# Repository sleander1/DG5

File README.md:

# DG5
An Arduino based, Kenwood DG5 emulator for the TS-520S

For more info, see http://www.kv6o.com/wordpress/projects/kenwood-dg5-emulator/

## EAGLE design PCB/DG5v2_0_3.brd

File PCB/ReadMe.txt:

See http://www.kv6o.com/wordpress/projects/kenwood-dg5-emulator/  for instructions on how to build, and notes on the construction.

Eagle files created using Eagle 7.1.0

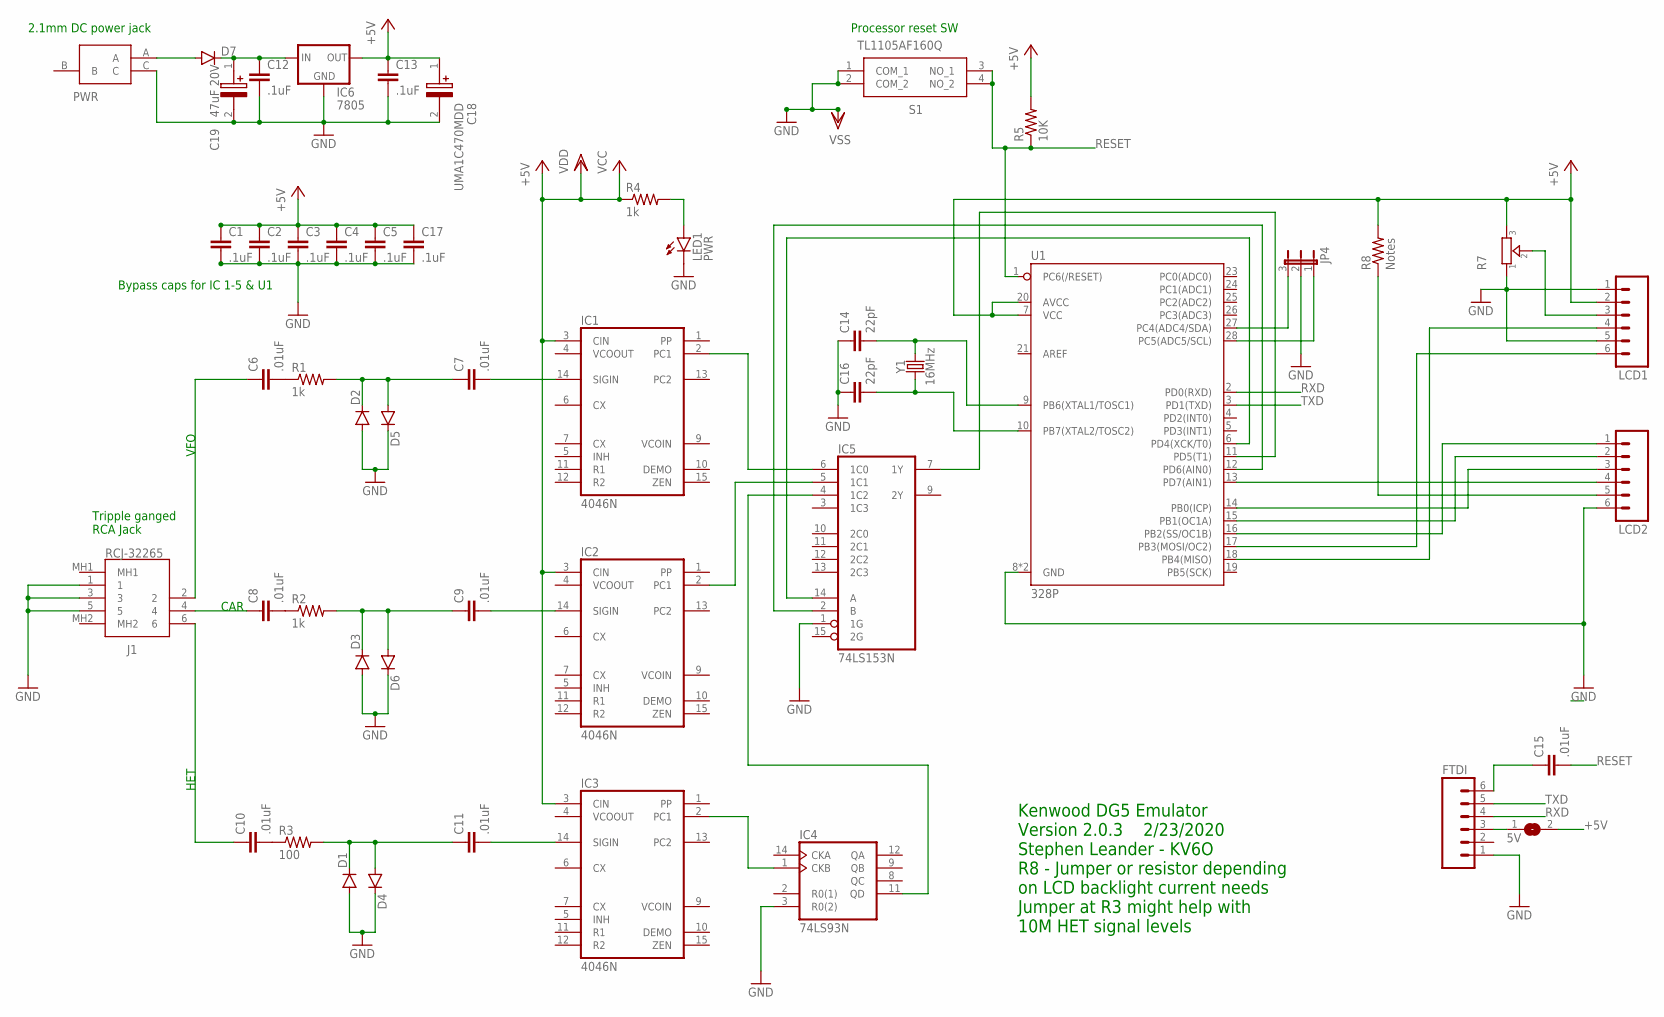
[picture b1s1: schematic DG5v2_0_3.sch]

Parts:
5V: SJ
C1, C2, C3, C4, C5, C12, C13, C17: .1uF; CAP-PTH-SMALL-KIT
C6, C7, C8, C9, C10, C11, C15: .01uF; CAP-PTH-SMALL-KIT
C14, C16: 22pF; CAP-PTH-SMALL
C18: UMA1C470MDD; CAPPRD250W45D680H600
C19: 47uF 20V; CAPPRD250W45D680H600
D1, D2, D3, D4, D5, D6: DIODE1N4148; DIODE-1N4148
D7: DIODE; DIODE-1N4001-KIT
FTDI: M06SIP; 1X06
IC1, IC2, IC3: 4046N; DIL16
IC4: 74LS93N; DIL14
IC5: 74LS153N; DIL16
IC6: 7805; TO220-IGO
J1: RCJ-32265; RCJ32265
JP4: JP2E; JP2
LCD1, LCD2: M06SIP; 1X06
LED1: PWR; LED3MM
PWR: 163-179PH-EX; 163179PHEX
R1, R2, R4: 1k; 1/6W-RES
R3: 100; 1/6W-RES
R5: 10K; 1/6W-RES
R7: TRIMMER-3306F; TRIMMER_3306F
R8: Notes; 1/6W-RES
S1: TL1105AF160Q
U1: 328P; DIP28
Y1: 16MHz; HC49US

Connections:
+5V: 5V.2, C1.1, C2.1, C3.1, C4.1, C5.1, C13.1, C17.1, C18.1 (+), IC1.3 (CIN), IC1.16 (VDD), IC2.3 (CIN), IC2.16 (VDD), IC3.3 (CIN), IC3.16 (VDD), IC4.5 (VCC), IC5.16 (VCC), IC6.OUT, LCD1.2, R4.1, R5.2, R7.3, R8.2, U1.7 (VCC), U1.20 (AVCC)
CAR: C8.1, J1.4
GND: C1.2, C2.2, C3.2, C4.2, C5.2, C12.2, C13.2, C14.1, C16.1, C17.2, C18.2 (-), C19.2 (-), D1.A, D2.A, D3.A, D4.C, D5.C, D6.C, FTDI.1, IC1.8 (VSS), IC2.8 (VSS), IC3.8 (VSS), IC4.3 (R0(2)), IC4.10 (GND), IC5.1 (1G), IC5.8 (GND), IC6.GND, J1.1, J1.3, J1.5, JP4.2, LCD1.1, LCD1.5, LCD2.6, LED1.K (C), PWR.C, R7.1, S1.1 (COM_1), S1.2 (COM_2), U1.8 (GND), U1.22 (GND)
HET: C10.1, J1.6
unnamed: C7.2, IC1.14 (SIGIN)
unnamed: IC1.2 (PC1), IC5.6 (1C0)
unnamed: IC2.2 (PC1), IC5.5 (1C1)
unnamed: C8.2, R2.1
unnamed: C6.2, R1.1
unnamed: C7.1, D2.C, D5.A, R1.2
unnamed: IC3.2 (PC1), IC4.1 (CKB)
unnamed: IC4.11 (QD), IC5.4 (1C2)
unnamed: C9.1, D3.C, D6.A, R2.2
unnamed: 5V.1, FTDI.3
unnamed: C9.2, IC2.14 (SIGIN)
unnamed: C11.2, IC3.14 (SIGIN)
unnamed: C11.1, D1.C, D4.A, R3.2
unnamed: C10.2, R3.1
unnamed: IC5.7 (1Y), U1.11 (PD5(T1))
unnamed: IC5.2 (B), U1.12 (PD6(AIN0))
unnamed: IC5.14 (A), U1.6 (PD4(XCK/T0))
unnamed: C14.2, U1.9 (PB6(XTAL1/TOSC1)), Y1.2
unnamed: LED1.A, R4.2
unnamed: JP4.3, U1.27 (PC4(ADC4/SDA))
unnamed: JP4.1, U1.28 (PC5(ADC5/SCL))
unnamed: C16.2, U1.10 (PB7(XTAL2/TOSC2)), Y1.1
unnamed: LCD2.5, R8.1
unnamed: LCD1.3, R7.2
unnamed: LCD1.4, U1.18 (PB4(MISO))
unnamed: LCD1.6, U1.17 (PB3(MOSI/OC2))
unnamed: C15.1, FTDI.6
unnamed: D7.A, PWR.A
unnamed: LCD2.1, U1.16 (PB2(SS/OC1B))
unnamed: LCD2.2, U1.15 (PB1(OC1A))
unnamed: LCD2.3, U1.14 (PB0(ICP))
unnamed: LCD2.4, U1.13 (PD7(AIN1))
RESET: C15.2, R5.1, S1.3 (NO_1), S1.4 (NO_2), U1.1 (PC6(/RESET))
RXD: FTDI.4, U1.2 (PD0(RXD))
TXD: FTDI.5, U1.3 (PD1(TXD))
VFO: C6.1, J1.2
VIN: C12.1, C19.1 (+), D7.C, IC6.IN

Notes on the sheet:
Kenwood DG5 Emulator Version 2.0.3 2/23/2020 Stephen Leander - KV6O R8 - Jumper or resistor depending on LCD backlight current needs Jumper at R3 might help with 10M HET signal levels
VFO
CAR
HET
Bypass caps for IC 1-5 & U1
Tripple ganged RCA Jack
2.1mm DC power jack
Processor reset SW

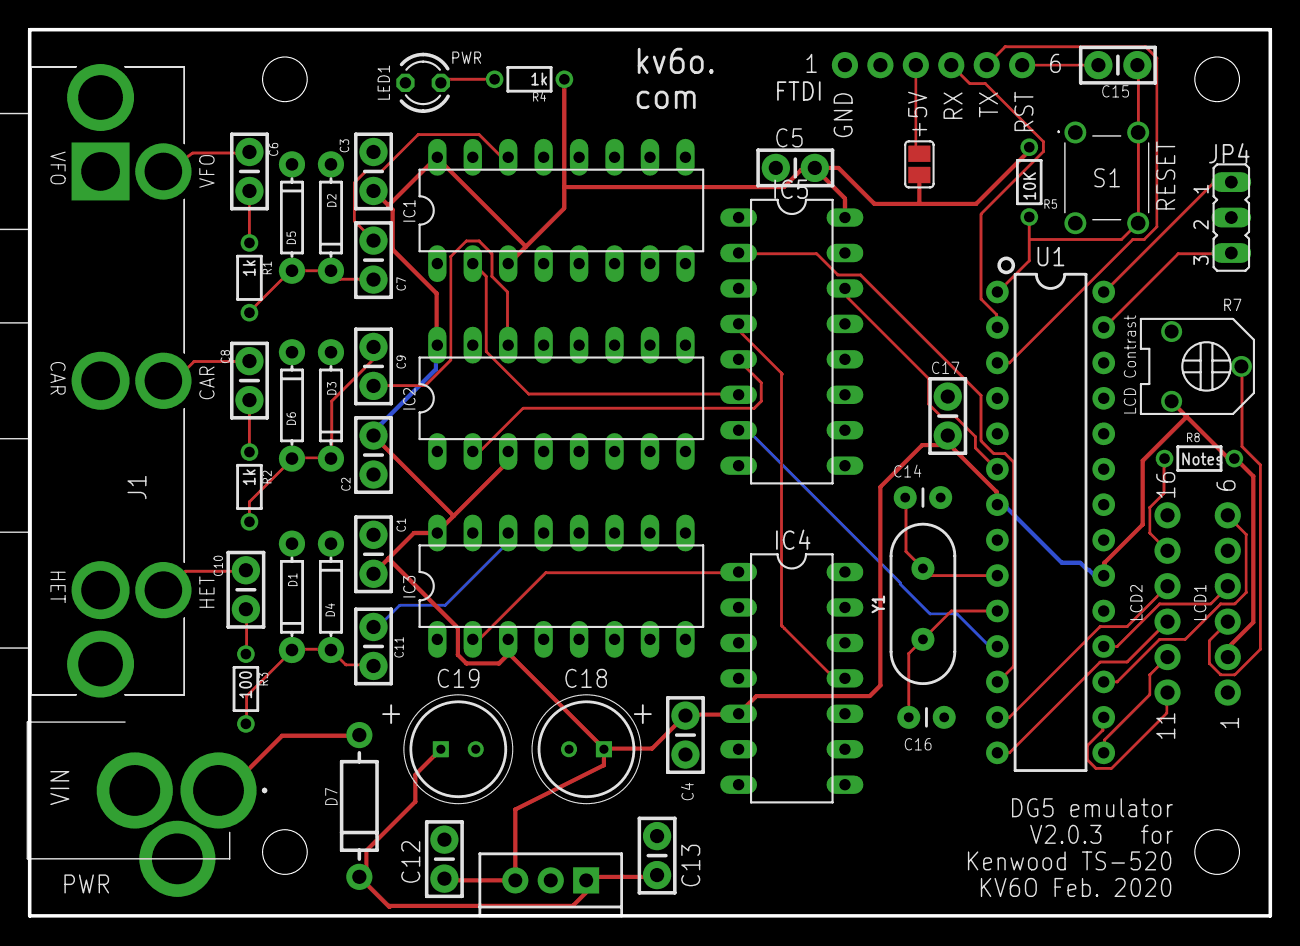
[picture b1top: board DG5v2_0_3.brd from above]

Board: 2 copper layers, 88.9 x 63.5 mm, 50 parts (0 on the bottom side), 41 nets.

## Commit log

2017-04-08 Create test
2018-05-19 Fix overflow in the printf target buffer that breaks display on at least the Uno clone I'm using.
2018-05-19 Ensure that the LCD enable line is low when we're not using it.
    This and the last commit allows my DG5 on an Uno board clone to work!
2020-03-14 Add files via upload
    Added missing 10k resistor, R5

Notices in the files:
parts and their libraries:
SparkFun-Passives: Licensing: Creative Commons ShareAlike 4.0 International - https://creativecommons.org/licenses/by-sa/4.0
SparkFun: Licensing: CC v3.0 Share-Alike You are welcome to use this library for commercial purposes.
